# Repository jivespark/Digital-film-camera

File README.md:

# Digital-film-camera
This is a project I made for the Hackclub stasis YSWS. It is a camera that uses the raspberry pi camera module 3 and a raspberry pi zero to take pictures. I made it be a bit like the older film cameras so you don't get a preview on a screen, only after you took the picture.

**Why did I make this project?**

I made this project since I like photography, and hardware design and thought this would be a nice way to blend them together. I also wanted to have a simple camera I could just slip in my backpack, and don't have to worry about settings, lenses, etc.I usually use my phone for this, but sometimes I just like to leave my phone at home and have a seperate device for taking photos.

Camera assembly:

Internal layout(for assembly):

Schematic:

PCB:

BOM:
|Name                            |Purpose                                                   |Quantity|Total Cost (USD)|Link                                                 |Distributor|
|--------------------------------|----------------------------------------------------------|--------|----------------|-----------------------------------------------------|-----------|
|Resistor kit                    |Resistors for power and buzzer control                    |1       |6.26            |https://www.aliexpress.com/item/1005009689760726.html|Aliexpress |
|Passive buzzer                  |A passive buzzer for audio feedback                       |1       |4.52            |https://www.aliexpress.com/item/1005009689760726.html|Aliexpress |
|Female header                   |A female header to connect the pi                         |1       |0.83            |https://www.aliexpress.com/item/32854215610.html     |Aliexpress |
|0805 1A 6V fuse                 |A fuse for safeguarding the power managment               |1       |1.48            |https://www.aliexpress.com/item/1005011924342826.html|Aliexpress |
|4.7UH 1210 inductor             |Inductor for the power managment circuit                  |1       |2.76            |https://www.aliexpress.com/item/1005006118890471.html|Aliexpress |
|100µF 25V electrolytic capacitor|A capacitor for voltage regulation                        |1       |1.26            |https://www.aliexpress.com/item/1005006192445408.html|Aliexpress |
|IP5306 chip                     |Charging and discharging the battery with boost conversion|1       |1.94            |https://www.aliexpress.com/item/1005007505994153.html|Aliexpress |
|0805 Ceramic capacitors         |Ceramic capacitors for power managment.                   |1       |7.45            |https://www.aliexpress.com/item/1005010516436707.html|Aliexpress |
|15 to 22 pin CSI cable          |A CSI cable to connect the pi and the camera              |1       |2.17            |https://www.aliexpress.com/item/1005006522239991.html|Aliexpress |
|Raspberry pi camera module 3    |Camera module for taking pictures                         |1       |32.00           |https://www.amazon.com/n/dp/B0C9PYCV9S/              |Amazon     |
|Raspberry pi zero 2WH           |The main microcontroller controlling everything           |1       |32.99           |https://www.amazon.com/dp/B0GJQMKJ4V                 |Amazon     |
|Usb-c connector                 |Usb-c connector for charging                              |1       |4.43            |https://www.aliexpress.com/item/1005010700033077.html|Aliexpress |

I aslo want to say that 2 MX switches and 1 18650 battery is also required, the reason they are not in the BOM is because I have them at home so I can use those and wont have to buy them.

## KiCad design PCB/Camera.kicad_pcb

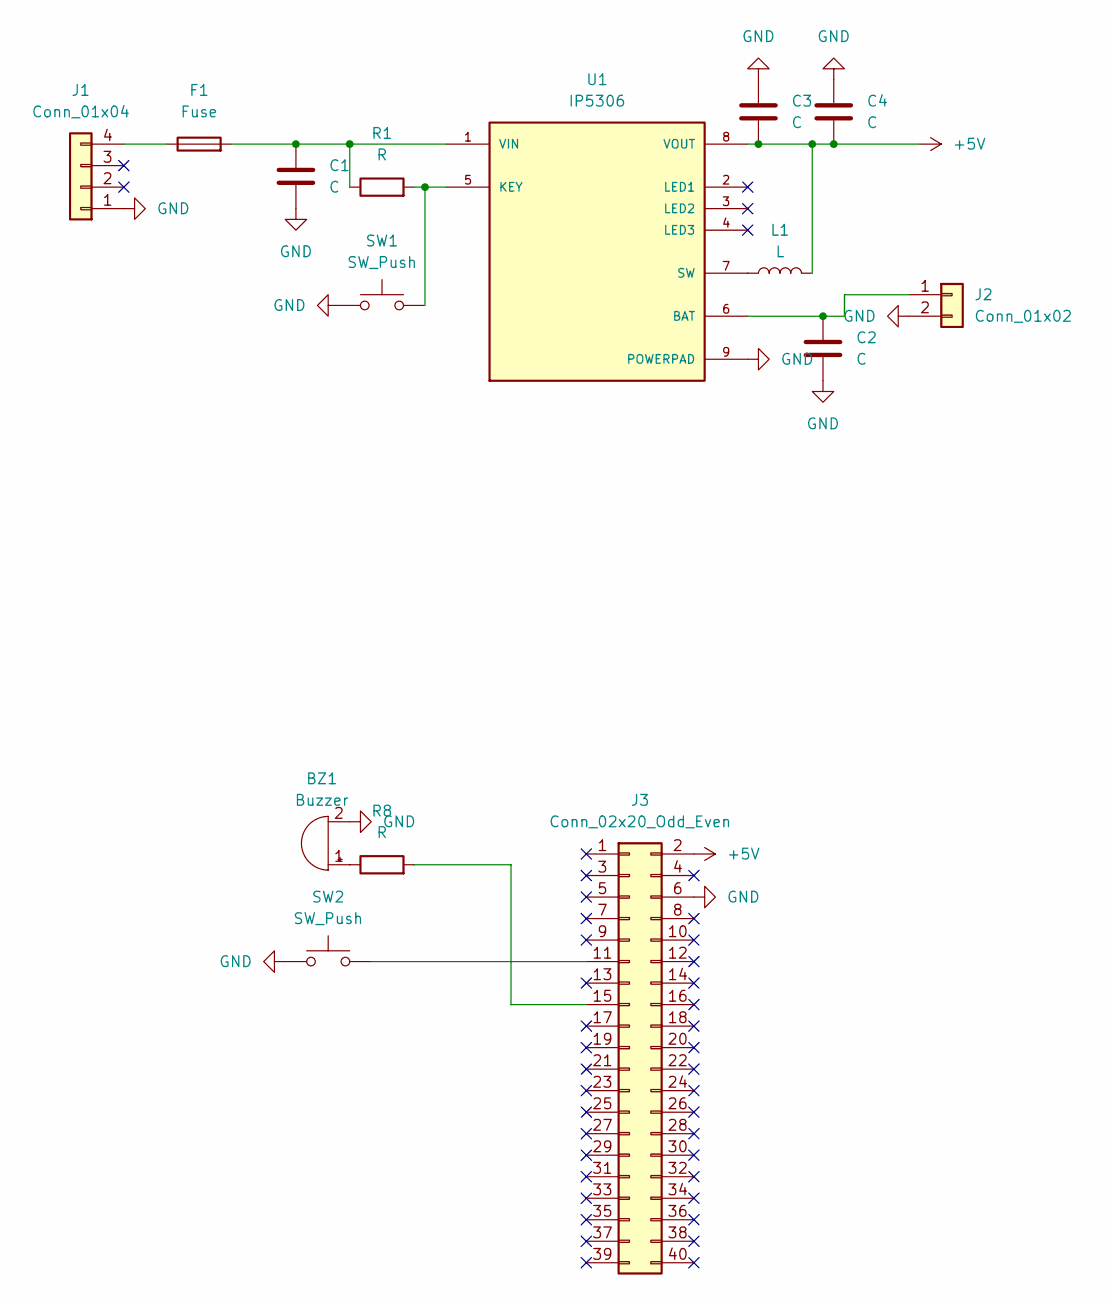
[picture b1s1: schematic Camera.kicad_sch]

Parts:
BZ1: Buzzer; Buzzer_TDK_PS1240P02BT_D12.2mm_H6.5mm
C1, C2, C4: C; C_0805_2012Metric
C3: C; CP_Radial_D5.0mm_P2.00mm
F1: Fuse; Fuse_0805_2012Metric
J1: Conn_01x04; PinHeader_1x04_P2.54mm_Vertical
J2: Conn_01x02; PinHeader_1x02_P2.54mm_Vertical
J3: Conn_02x20_Odd_Even; PinSocket_2x20_P2.54mm_Vertical
L1: L; L_0805_2012Metric
R1, R8: R; R_0805_2012Metric
SW1, SW2: SW_Push; SW_Cherry_MX_1.00u_PCB
U1: IP5306; SOP127P600X165-9N; PARTREV 1.31

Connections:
+5V: C3.1, C4.2, J3.2, L1.2, U1.8 (VOUT)
GND: BZ1.2 (-), C1.1, C2.2, C3.2, C4.1, J1.1, J2.2, J3.6, SW1.1, SW2.1, U1.9 (POWERPAD)
unnamed: BZ1.1 (+), R8.1
unnamed: F1.1, J1.4
unnamed: C2.1, J2.1, U1.6 (BAT)
unnamed: J3.11, SW2.2
unnamed: J3.15, R8.2
unnamed: R1.2, SW1.2, U1.5 (KEY)
unnamed: L1.1, U1.7 (SW)
unnamed: C1.2, F1.2, R1.1, U1.1 (VIN)

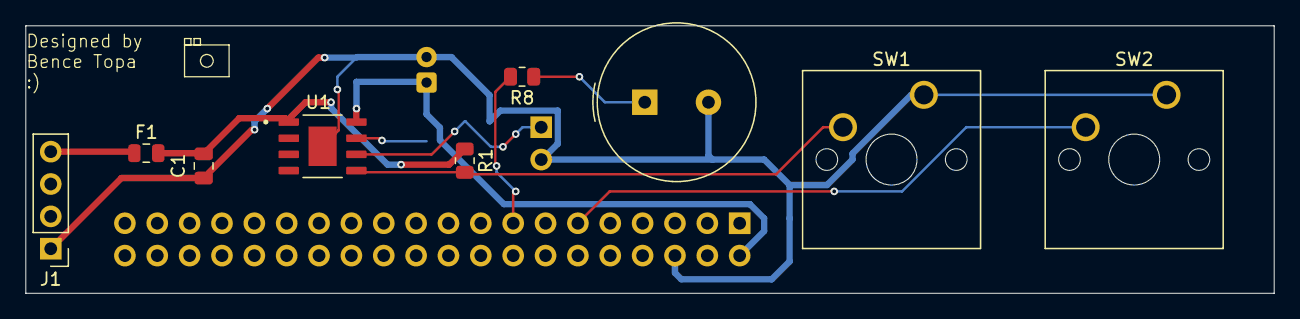
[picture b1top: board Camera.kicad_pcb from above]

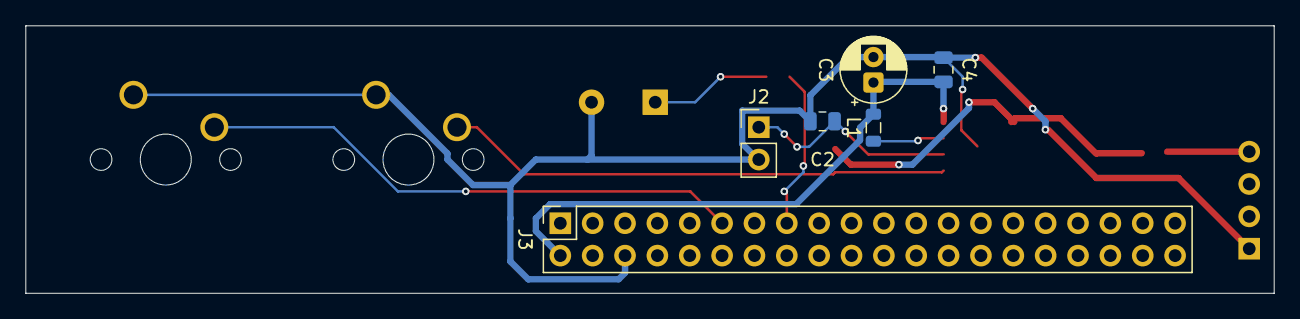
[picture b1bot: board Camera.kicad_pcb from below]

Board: 2 copper layers, 98.0 x 21.0 mm, 15 parts (6 on the bottom side), 10 nets.

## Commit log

2026-04-09 Add initial implementation of buzzer, camera, main, and storage modules
2026-04-09 Created the logic for the buzzer to be able to make different sounds
2026-04-09 Made storage handling logic
2026-04-10 Added the files for the PCB and the case
2026-04-10 Added pictures
2026-04-10 Wrote README
2026-04-10 Wrote markdown files
2026-04-10 Update README with additional component requirements
